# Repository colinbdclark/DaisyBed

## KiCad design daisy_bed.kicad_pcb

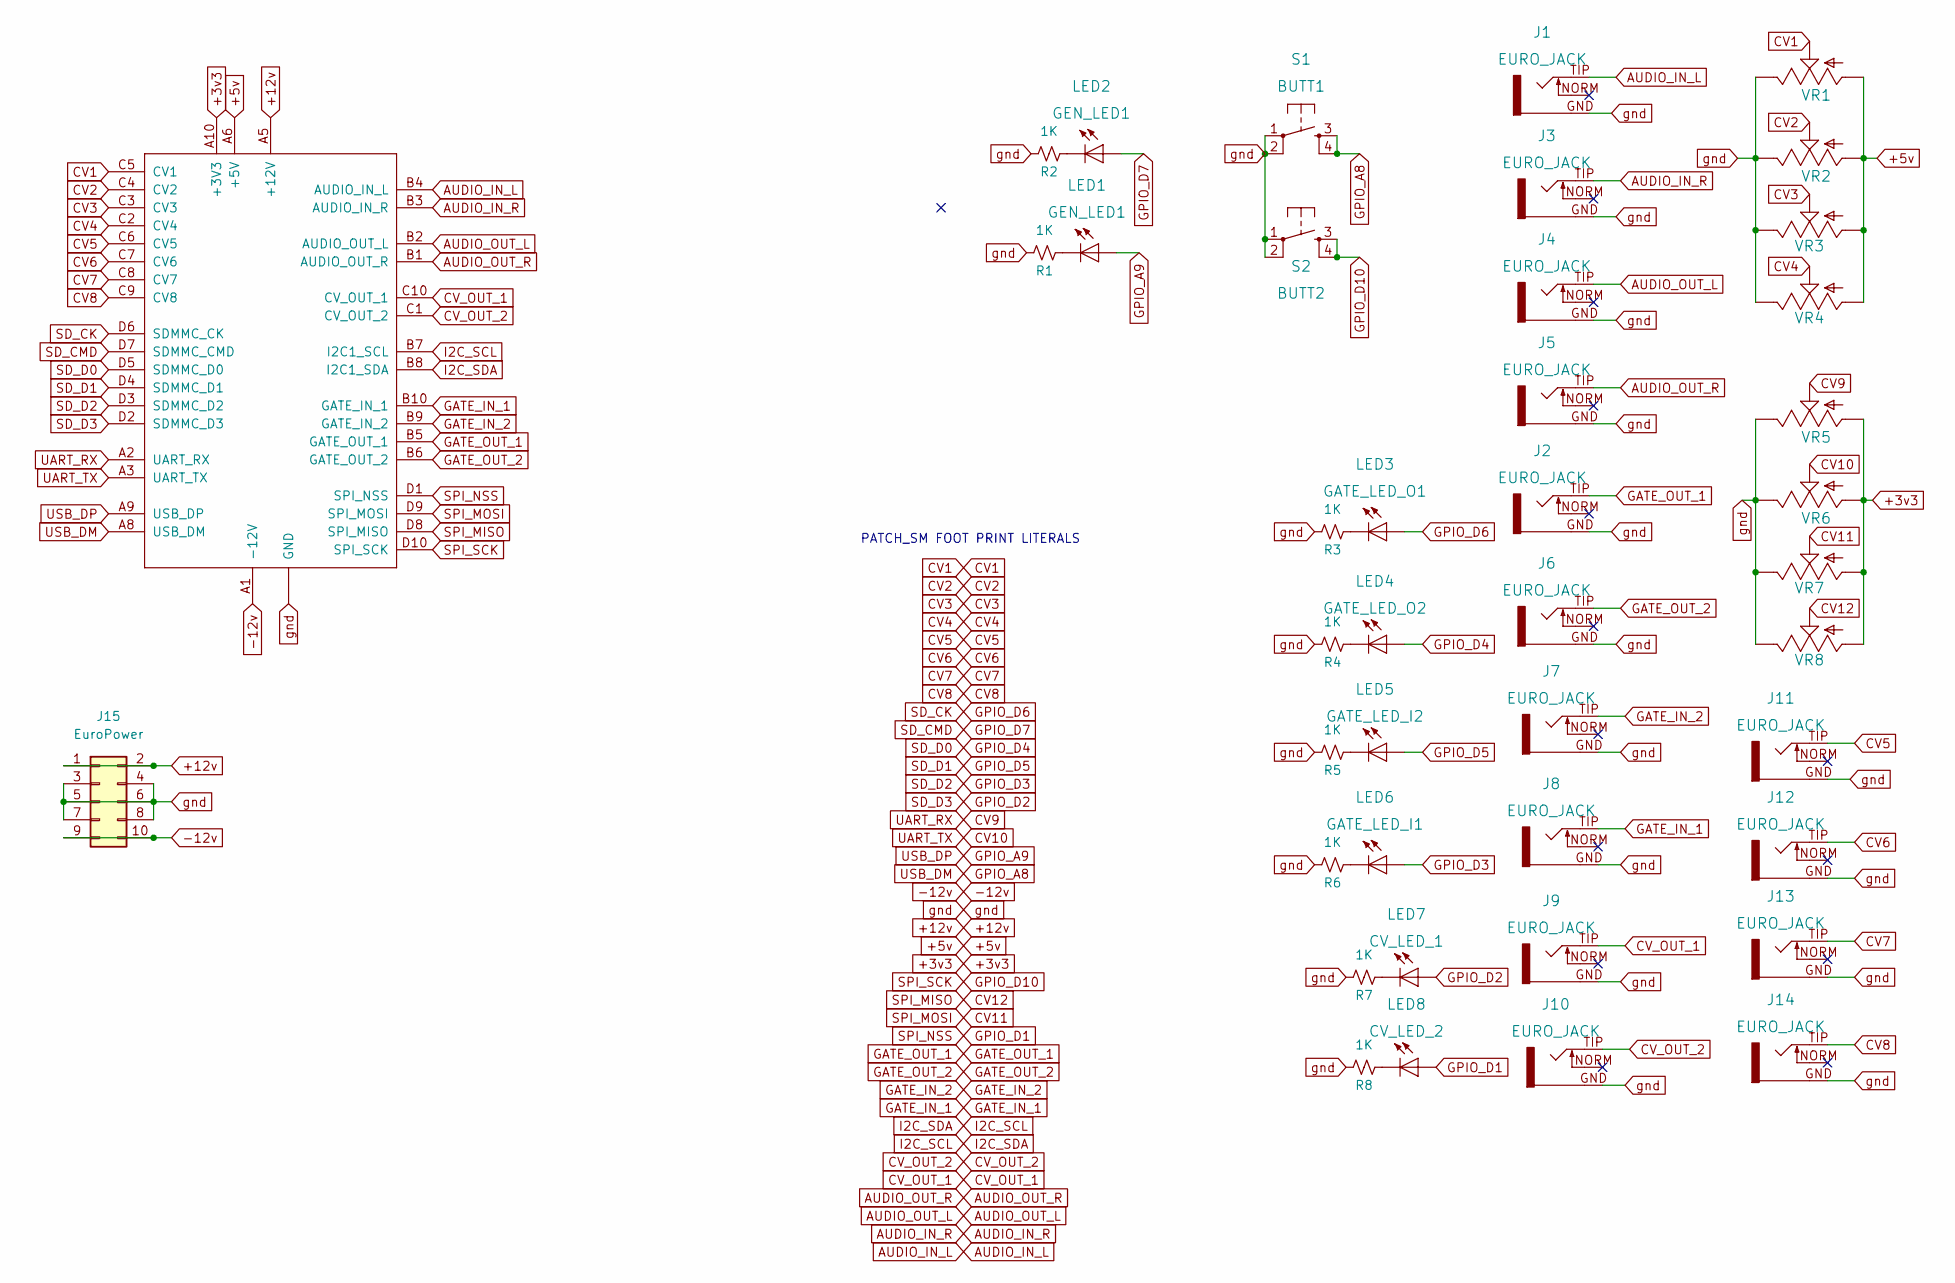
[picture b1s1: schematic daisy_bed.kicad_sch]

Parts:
J1, J2, J3, J4, J5, J6, J7, J8, J9, J10, J11, J12, J13, J14: EURO_JACK; S_JACK
J15: EuroPower; PinHeader_2x05_P2.54mm_Vertical
LED1, LED2: GEN_LED1; LED
LED3: GATE_LED_O1; LED
LED4: GATE_LED_O2; LED
LED5: GATE_LED_I2; LED
LED6: GATE_LED_I1; LED
LED7: CV_LED_1; LED
LED8: CV_LED_2; LED
R1, R2, R3, R4, R5, R6, R7, R8: 1K; Resistor_L6.3mm_D2.5mm_P7.62mm_Horizontal
S1: BUTT1; TL1105SPF250Q_SILK
S2: BUTT2; TL1105SPF250Q_SILK
U1: ES_DAISY_PATCH_SM_REV1
VR1, VR2, VR3, VR4, VR5, VR6, VR7, VR8: POT_9MM_SNAP-IN_; Potentiometer_RV09

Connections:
+3v3: U1.A10 (+3V3), VR5.1, VR6.1, VR7.1, VR8.1
+5v: U1.A6 (+5V), VR1.1, VR2.1, VR3.1, VR4.1
+12v: J15.1, J15.2, U1.A5 (+12V)
-12v: J15.9, J15.10, U1.A1 (-12V)
AUDIO_IN_L: J1.TIP, U1.B4 (AUDIO_IN_L)
AUDIO_IN_R: J3.TIP, U1.B3 (AUDIO_IN_R)
AUDIO_OUT_L: J4.TIP, U1.B2 (AUDIO_OUT_L)
AUDIO_OUT_R: J5.TIP, U1.B1 (AUDIO_OUT_R)
CV1: U1.C5 (CV1), VR1.2
CV2: U1.C4 (CV2), VR2.2
CV3: U1.C3 (CV3), VR3.2
CV4: U1.C2 (CV4), VR4.2
CV5: J11.TIP, U1.C6 (CV5)
CV6: J12.TIP, U1.C7 (CV6)
CV7: J13.TIP, U1.C8 (CV7)
CV8: J14.TIP, U1.C9 (CV8)
CV9: U1.A2 (UART_RX), VR5.2
CV10: U1.A3 (UART_TX), VR6.2
CV11: U1.D9 (SPI_MOSI), VR7.2
CV12: U1.D8 (SPI_MISO), VR8.2
CV_OUT_1: J9.TIP, U1.C10 (CV_OUT_1)
CV_OUT_2: J10.TIP, U1.C1 (CV_OUT_2)
GATE_IN_1: J8.TIP, U1.B10 (GATE_IN_1)
GATE_IN_2: J7.TIP, U1.B9 (GATE_IN_2)
GATE_OUT_1: J2.TIP, U1.B5 (GATE_OUT_1)
GATE_OUT_2: J6.TIP, U1.B6 (GATE_OUT_2)
GPIO_A8: S1.3, S1.4, U1.A8 (USB_DM)
GPIO_A9: LED1.A, U1.A9 (USB_DP)
GPIO_D1: LED8.A, U1.D1 (SPI_NSS)
GPIO_D2: LED7.A, U1.D2 (SDMMC_D3)
GPIO_D3: LED6.A, U1.D3 (SDMMC_D2)
GPIO_D4: LED4.A, U1.D5 (SDMMC_D0)
GPIO_D5: LED5.A, U1.D4 (SDMMC_D1)
GPIO_D6: LED3.A, U1.D6 (SDMMC_CK)
GPIO_D7: LED2.A, U1.D7 (SDMMC_CMD)
GPIO_D10: S2.3, S2.4, U1.D10 (SPI_SCK)
I2C_SCL: U1.B7 (I2C1_SCL), U1.B8 (I2C1_SDA)
unnamed: LED1.K (C), R1.2
unnamed: LED2.K (C), R2.2
unnamed: LED3.K (C), R3.2
unnamed: LED4.K (C), R4.2
unnamed: LED5.K (C), R5.2
unnamed: LED6.K (C), R6.2
unnamed: LED7.K (C), R7.2
unnamed: LED8.K (C), R8.2
gnd: J1.GND, J2.GND, J3.GND, J4.GND, J5.GND, J6.GND, J7.GND, J8.GND, J9.GND, J10.GND, J11.GND, J12.GND, J13.GND, J14.GND, J15.3, J15.4, J15.5, J15.6, J15.7, J15.8, R1.1, R2.1, R3.1, R4.1, R5.1, R6.1, R7.1, R8.1, S1.1, S1.2, S2.1, S2.2, U1.A4 (GND), U1.A7 (GND), VR1.3, VR2.3, VR3.3, VR4.3, VR5.3, VR6.3, VR7.3, VR8.3

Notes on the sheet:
PATCH_SM FOOT PRINT LITERALS

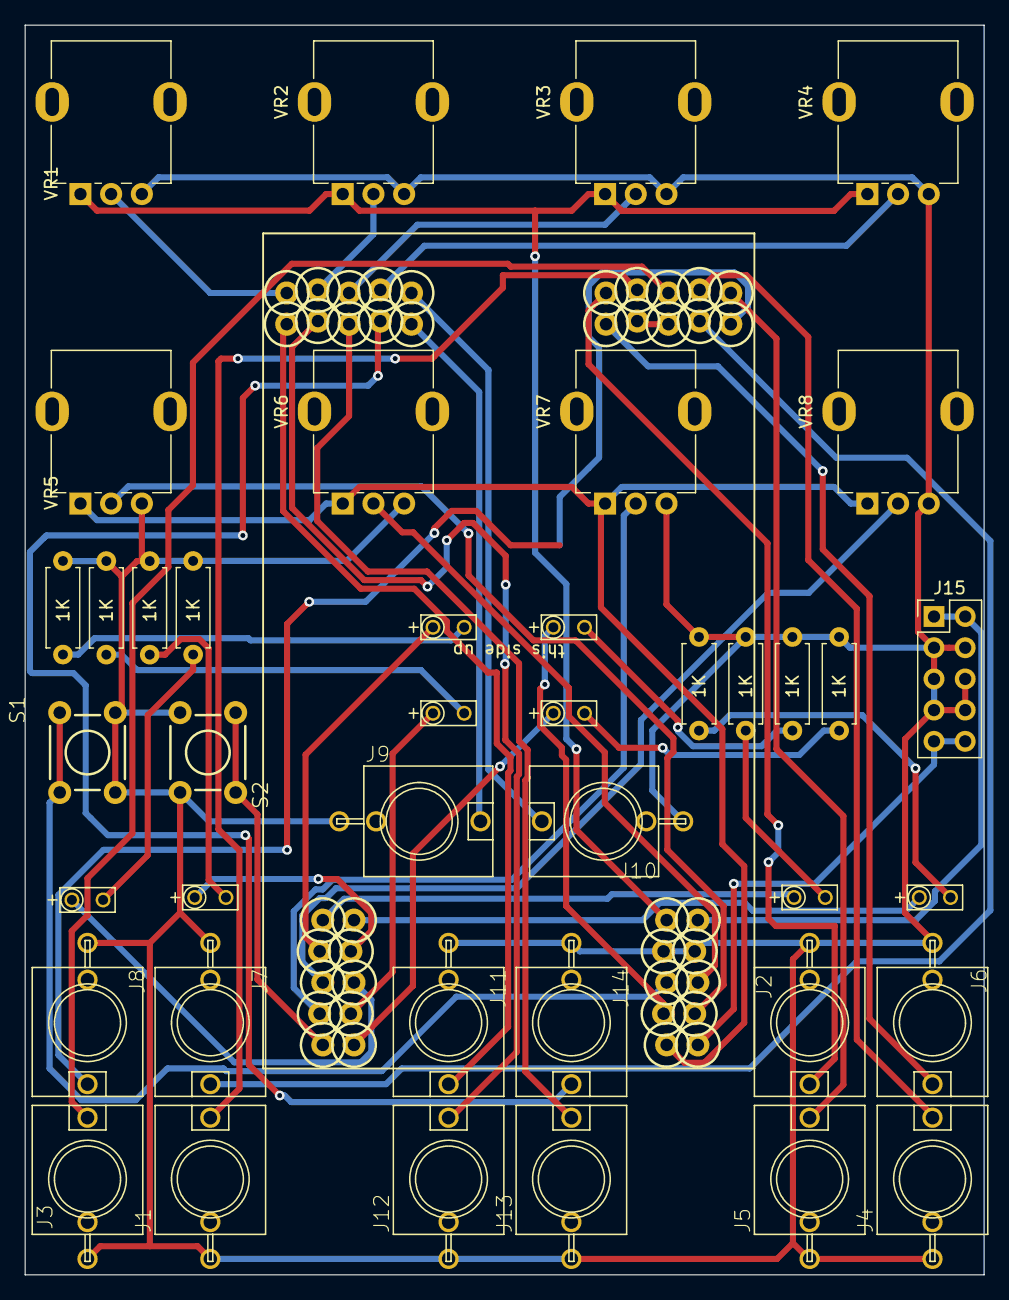
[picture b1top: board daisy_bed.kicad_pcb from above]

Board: 2 copper layers, 78.1 x 101.8 mm, 42 parts (0 on the bottom side), 46 nets.

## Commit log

2023-10-07 Removes old panel project. Updates projects to KiCad 7.
2023-10-07 Updates schematic and PCB file to KiCad 7.
2023-10-07 Moves top left corner of PCB to 50,50mm.
2023-10-07 Centres the potentiometers on the board; narrows the PCB to 78.025mm.
2023-10-07 Aligns all jacks.
